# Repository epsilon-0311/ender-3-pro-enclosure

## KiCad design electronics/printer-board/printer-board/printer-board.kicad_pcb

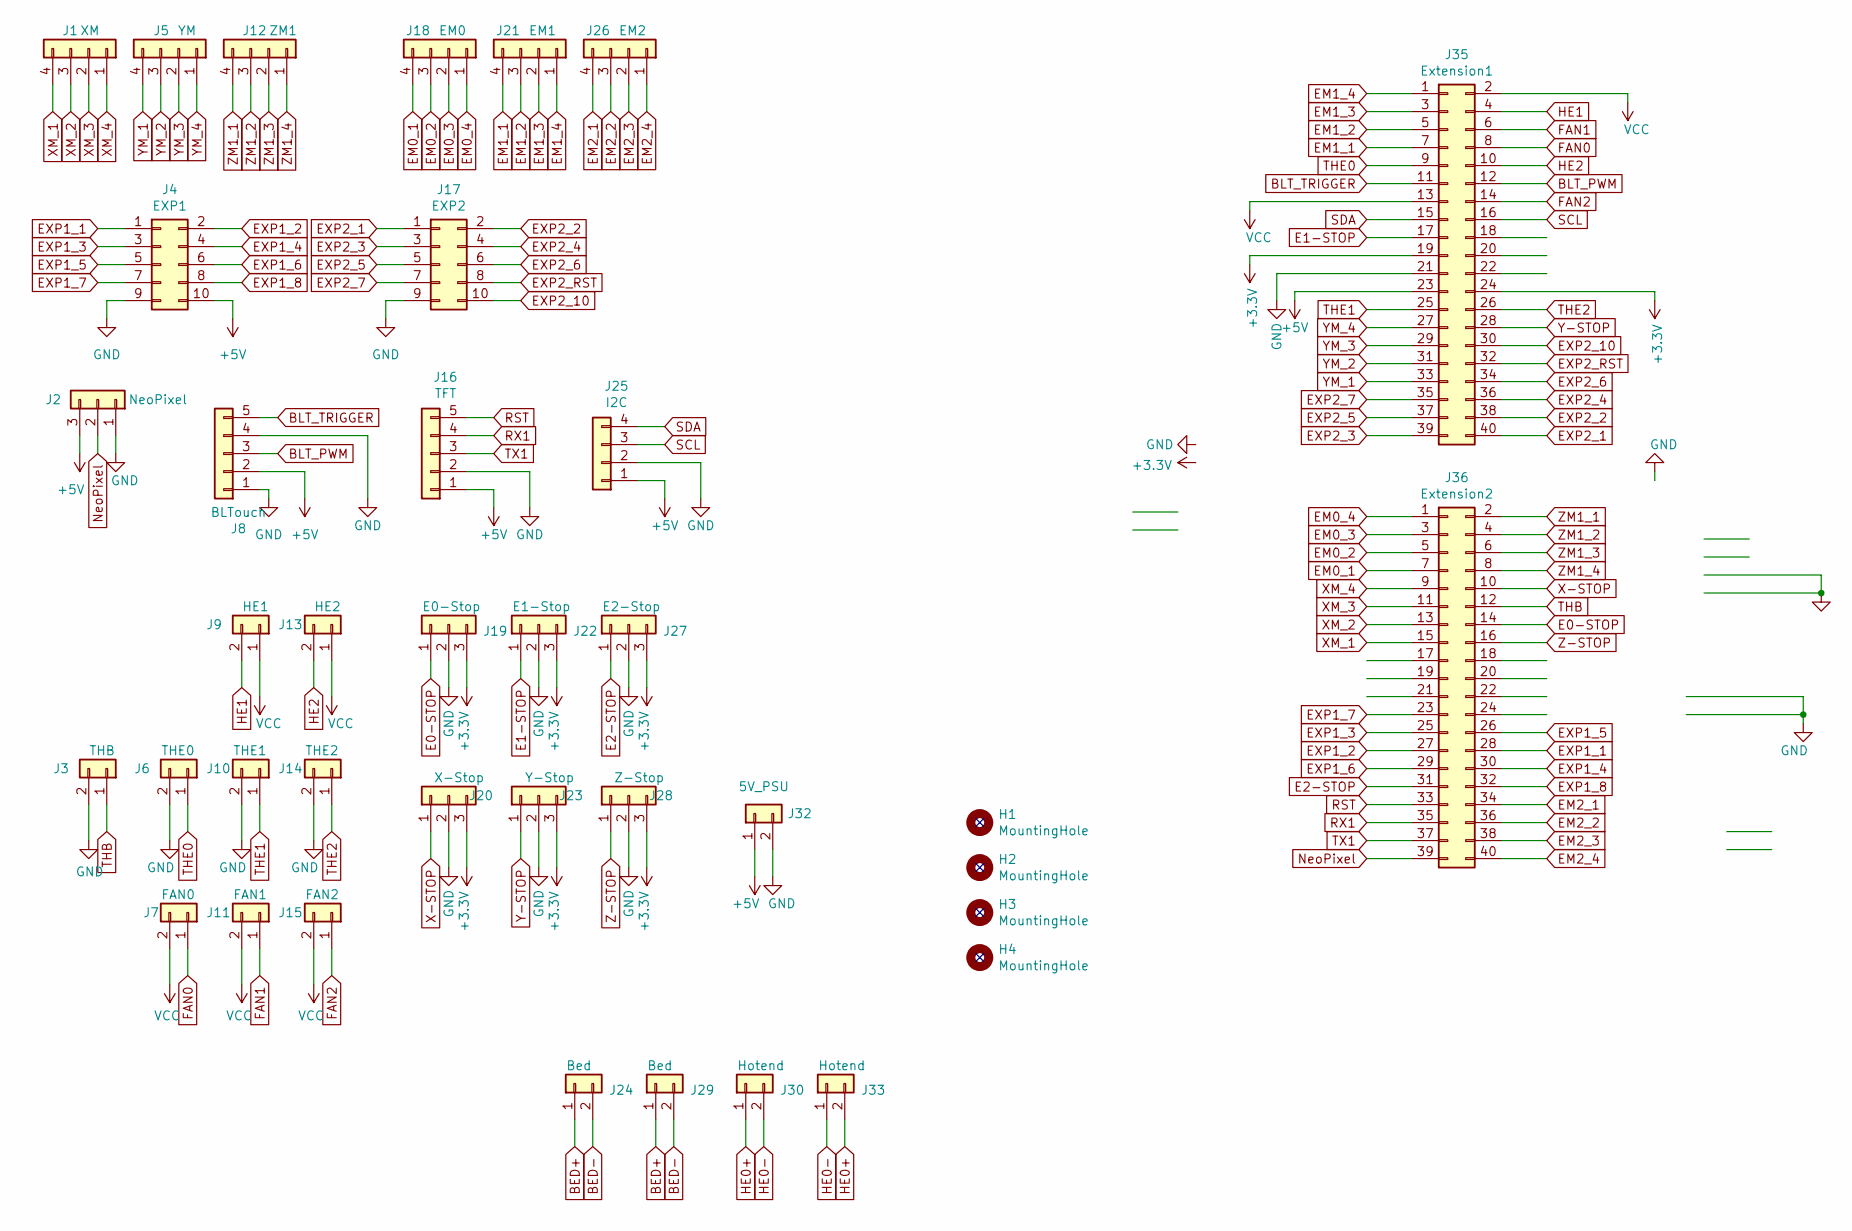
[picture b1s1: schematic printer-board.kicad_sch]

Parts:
H1, H2, H3, H4: MountingHole; MountingHole_3.2mm_M3
J1: XM; JST_XH_B4B-XH-A_1x04_P2.50mm_Vertical
J2: NeoPixel; PhoenixContact_MSTBA_2,5_3-G_1x03_P5.00mm_Horizontal
J3: THB; JST_XH_B2B-XH-A_1x02_P2.50mm_Vertical
J4: EXP1; IDC-Header_2x05_P2.54mm_Vertical
J5: YM; JST_XH_B4B-XH-A_1x04_P2.50mm_Vertical
J6: THE0; JST_XH_B2B-XH-A_1x02_P2.50mm_Vertical
J7: FAN0; JST_XH_B2B-XH-A_1x02_P2.50mm_Vertical
J8: BLTouch; JST_XH_B5B-XH-A_1x05_P2.50mm_Vertical
J9: HE1; JST_XH_B2B-XH-A_1x02_P2.50mm_Vertical
J10: THE1; JST_XH_B2B-XH-A_1x02_P2.50mm_Vertical
J11: FAN1; JST_XH_B2B-XH-A_1x02_P2.50mm_Vertical
J12: ZM1; JST_XH_B4B-XH-A_1x04_P2.50mm_Vertical
J13: HE2; JST_XH_B2B-XH-A_1x02_P2.50mm_Vertical
J14: THE2; JST_XH_B2B-XH-A_1x02_P2.50mm_Vertical
J15: FAN2; JST_XH_B2B-XH-A_1x02_P2.50mm_Vertical
J16: TFT; JST_XH_B5B-XH-A_1x05_P2.50mm_Vertical
J17: EXP2; IDC-Header_2x05_P2.54mm_Vertical
J18: EM0; JST_XH_B4B-XH-A_1x04_P2.50mm_Vertical
J19: E0-Stop; JST_XH_B3B-XH-A_1x03_P2.50mm_Vertical
J20: X-Stop; JST_XH_B3B-XH-A_1x03_P2.50mm_Vertical
J21: EM1; JST_XH_B4B-XH-A_1x04_P2.50mm_Vertical
J22: E1-Stop; JST_XH_B3B-XH-A_1x03_P2.50mm_Vertical
J23: Y-Stop; JST_XH_B3B-XH-A_1x03_P2.50mm_Vertical
J24, J29: Bed; PhoenixContact_MSTBA_2,5_2-G_1x02_P5.00mm_Horizontal
J25: I2C; JST_XH_B4B-XH-A_1x04_P2.50mm_Vertical
J26: EM2; JST_XH_B4B-XH-A_1x04_P2.50mm_Vertical
J27: E2-Stop; JST_XH_B3B-XH-A_1x03_P2.50mm_Vertical
J28: Z-Stop; JST_XH_B3B-XH-A_1x03_P2.50mm_Vertical
J30, J33: Hotend; PhoenixContact_MSTBA_2,5_2-G_1x02_P5.00mm_Horizontal
J32: 5V_PSU; PhoenixContact_MSTBA_2,5_2-G_1x02_P5.00mm_Horizontal
J35: Extension1; IDC-Header_2x20_P2.54mm_Vertical
J36: Extension2; IDC-Header_2x20_P2.54mm_Vertical

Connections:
+3V3: J19.3, J20.3, J22.3, J23.3, J27.3, J28.3, J35.19, J35.24
+5V: J2.3, J4.10, J8.2, J16.1, J25.1, J32.1, J35.23
BED+: J24.1, J29.1
BED-: J24.2, J29.2
BLT_PWM: J8.3, J35.12
BLT_TRIGGER: J8.5, J35.11
E0-STOP: J19.1, J36.14
E1-STOP: J22.1, J35.17
E2-STOP: J27.1, J36.31
EM0_1: J18.4, J36.7
EM0_2: J18.3, J36.5
EM0_3: J18.2, J36.3
EM0_4: J18.1, J36.1
EM1_1: J21.4, J35.7
EM1_2: J21.3, J35.5
EM1_3: J21.2, J35.3
EM1_4: J21.1, J35.1
EM2_1: J26.4, J36.34
EM2_2: J26.3, J36.36
EM2_3: J26.2, J36.38
EM2_4: J26.1, J36.40
EXP1_1: J4.1, J36.28
EXP1_2: J4.2, J36.27
EXP1_3: J4.3, J36.25
EXP1_4: J4.4, J36.30
EXP1_5: J4.5, J36.26
EXP1_6: J4.6, J36.29
EXP1_7: J4.7, J36.23
EXP1_8: J4.8, J36.32
EXP2_1: J17.1, J35.40
EXP2_2: J17.2, J35.38
EXP2_3: J17.3, J35.39
EXP2_4: J17.4, J35.36
EXP2_5: J17.5, J35.37
EXP2_6: J17.6, J35.34
EXP2_7: J17.7, J35.35
EXP2_10: J17.10, J35.30
EXP2_RST: J17.8, J35.32
FAN0: J7.1, J35.8
FAN1: J11.1, J35.6
FAN2: J15.1, J35.14
GND: J2.1, J3.2, J4.9, J6.2, J8.1, J8.4, J10.2, J14.2, J16.2, J17.9, J19.2, J20.2, J22.2, J23.2, J25.2, J27.2, J28.2, J32.2, J35.21
HE0+: J30.1, J33.2
HE0-: J30.2, J33.1
HE1: J9.2, J35.4
HE2: J13.2, J35.10
NeoPixel: J2.2, J36.39
RST: J16.5, J36.33
RX1: J16.4, J36.35
SCL: J25.3, J35.16
SDA: J25.4, J35.15
THB: J3.1, J36.12
THE0: J6.1, J35.9
THE1: J10.1, J35.25
THE2: J14.1, J35.26
TX1: J16.3, J36.37
VCC: J7.2, J9.1, J11.2, J13.1, J15.2, J35.2, J35.13
X-STOP: J20.1, J36.10
XM_1: J1.4, J36.15
XM_2: J1.3, J36.13
XM_3: J1.2, J36.11
XM_4: J1.1, J36.9
Y-STOP: J23.1, J35.28
YM_1: J5.4, J35.33
YM_2: J5.3, J35.31
YM_3: J5.2, J35.29
YM_4: J5.1, J35.27
Z-STOP: J28.1, J36.16
ZM1_1: J12.4, J36.2
ZM1_2: J12.3, J36.4
ZM1_3: J12.2, J36.6
ZM1_4: J12.1, J36.8

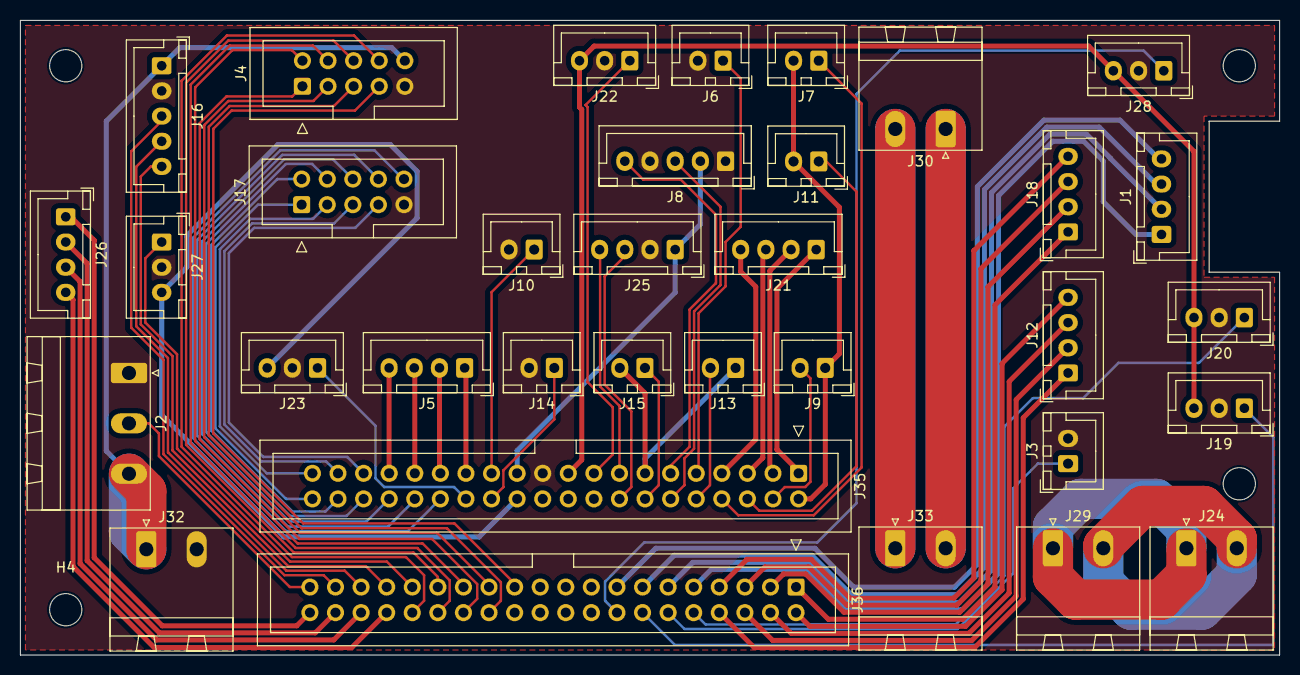
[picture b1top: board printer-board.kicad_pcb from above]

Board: 2 copper layers, 125.0 x 63.0 mm, 38 parts (0 on the bottom side), 72 nets.

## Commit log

2023-12-15 updated routing
